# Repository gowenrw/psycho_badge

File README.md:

# psycho_badge

This is where all the files for psycho_badge will be stored.

This includes code and art and cad and fab files.  All the things.

## File Structure

This is the file structure of this repository

* [/](/README.md) <- YOU ARE HERE
* [/3d_parts/](./3d_parts/) - 3D models of parts used in this project
* [/art/](./art/) - Artwork and other graphics created by this project
  * [/art/fonts/](./art/fonts/) - Fonts used in art and graphics
  * [/art/inspiration/](./art/inspiration/) - Art and graphics pulled from other sources used as inspiration for this project
  * [/art/logos/](./art/logos/) - Logos used in this project
* [/code/](./code/) - All project related Code / Firmware
* [/docs/](./docs/) - Documentation created by this project including web pages
* [/eda/](./eda/) - Electronic Design Automation files (i.e. KiCad)
  * [/eda/psycho_badge/](./eda/psycho_badge/) - KiCad 9.x project folder for the psycho_badge PCB
* [/reference_parts/](./reference_parts/) - Submodule of Third Party Documentation related to components
* [./README.md](/README.md) - This File
* [./LICENSE](/LICENSE) - Currently set to MIT

Note: the reference_parts directory is a link to a submodule repository.
To add it use the following cmd after cloning this:
```
git submodule add https://github.com/gowenrw/reference_parts reference_parts
```
This will make a link to the current commit of that repo.
To update it to a newer commit after its been added use this cmd:
```
git submodule update --init --recursive
```

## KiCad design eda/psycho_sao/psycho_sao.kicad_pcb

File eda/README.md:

# Electronic Design Automation

This is where all the Electronic Design Automation files for the PCB(s) will be stored.
The EDA used is KiCad 9.x unless otherwise specified.

The KiCad projects have been configured to use local libraries for long term sustainability per the best practices listed [HERE](https://hackaday.com/2017/05/18/kicad-best-practises-library-management/) and elsewhere.

## File Structure

This is the file structure of this repository

* [/](/README.md) - Home
* [/eda](/eda/) - Electronic Design Automation files - YOU ARE HERE
  * [/eda/psycho_badge/](/eda/psycho_badge/) - KiCad 9.x project folder for the psycho_badge PCB
    * ./3d_models/ - This directory contains footprint 3d model files
    * ./gerber/ - This directory contains gerber formatted files for manufacturing
    * ./lib_fp/ - This directory contains footprint module directories
    * ./lib_sh/ - This directory contains schematic library files
    * ./snapshots/ - This directory contains prints of schematic / cad files and images of preview / final product
  * [/eda/psycho_sao/](/eda/psycho_sao/) - KiCad 9.x project folder for the psycho_badge SAO PCBs
    * ./3d_models/ - This directory contains footprint 3d model files
    * ./gerber/ - This directory contains gerber formatted files for manufacturing
    * ./lib_fp/ - This directory contains footprint module directories
    * ./lib_sh/ - This directory contains schematic library files
    * ./snapshots/ - This directory contains prints of schematic / cad files and images of preview / final product

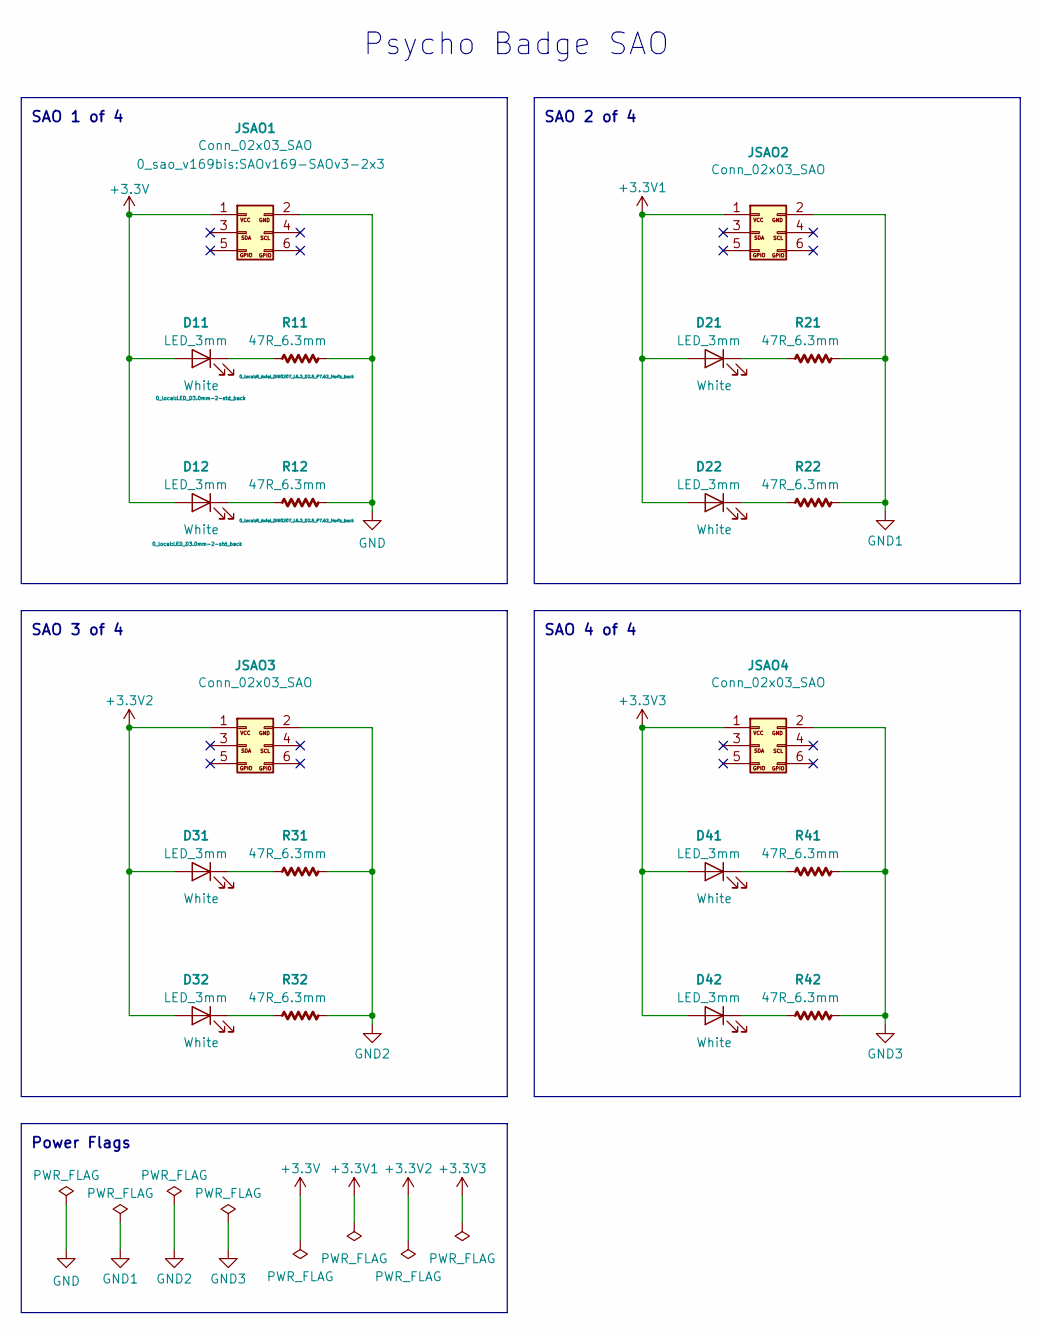
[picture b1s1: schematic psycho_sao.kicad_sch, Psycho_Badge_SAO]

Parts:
D11, D12, D21, D22, D31, D32, D41, D42: LED_3mm; LED_D3.0mm-2-std_back
JSAO1, JSAO2, JSAO3, JSAO4: Conn_02x03_SAO; SAOv169-SAOv3-2x3
R11, R12, R21, R22, R31, R32, R41, R42: 47R_6.3mm; R_Axial_DIN0207_L6.3_D2.5_P7.62_Horiz_back

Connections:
+3.3V: D11.2 (A), D12.2 (A), JSAO1.1
+3.3V1: D21.2 (A), D22.2 (A), JSAO2.1
+3.3V2: D31.2 (A), D32.2 (A), JSAO3.1
+3.3V3: D41.2 (A), D42.2 (A), JSAO4.1
GND: JSAO1.2, R11.2, R12.2
GND1: JSAO2.2, R21.2, R22.2
GND2: JSAO3.2, R31.2, R32.2
GND3: JSAO4.2, R41.2, R42.2
unnamed: D11.1 (K), R11.1
unnamed: D12.1 (K), R12.1
unnamed: D21.1 (K), R21.1
unnamed: D22.1 (K), R22.1
unnamed: D31.1 (K), R31.1
unnamed: D32.1 (K), R32.1
unnamed: D41.1 (K), R41.1
unnamed: D42.1 (K), R42.1

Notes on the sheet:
SAO 1 of 4
SAO 4 of 4
Psycho Badge SAO
Power Flags
SAO 3 of 4
SAO 2 of 4

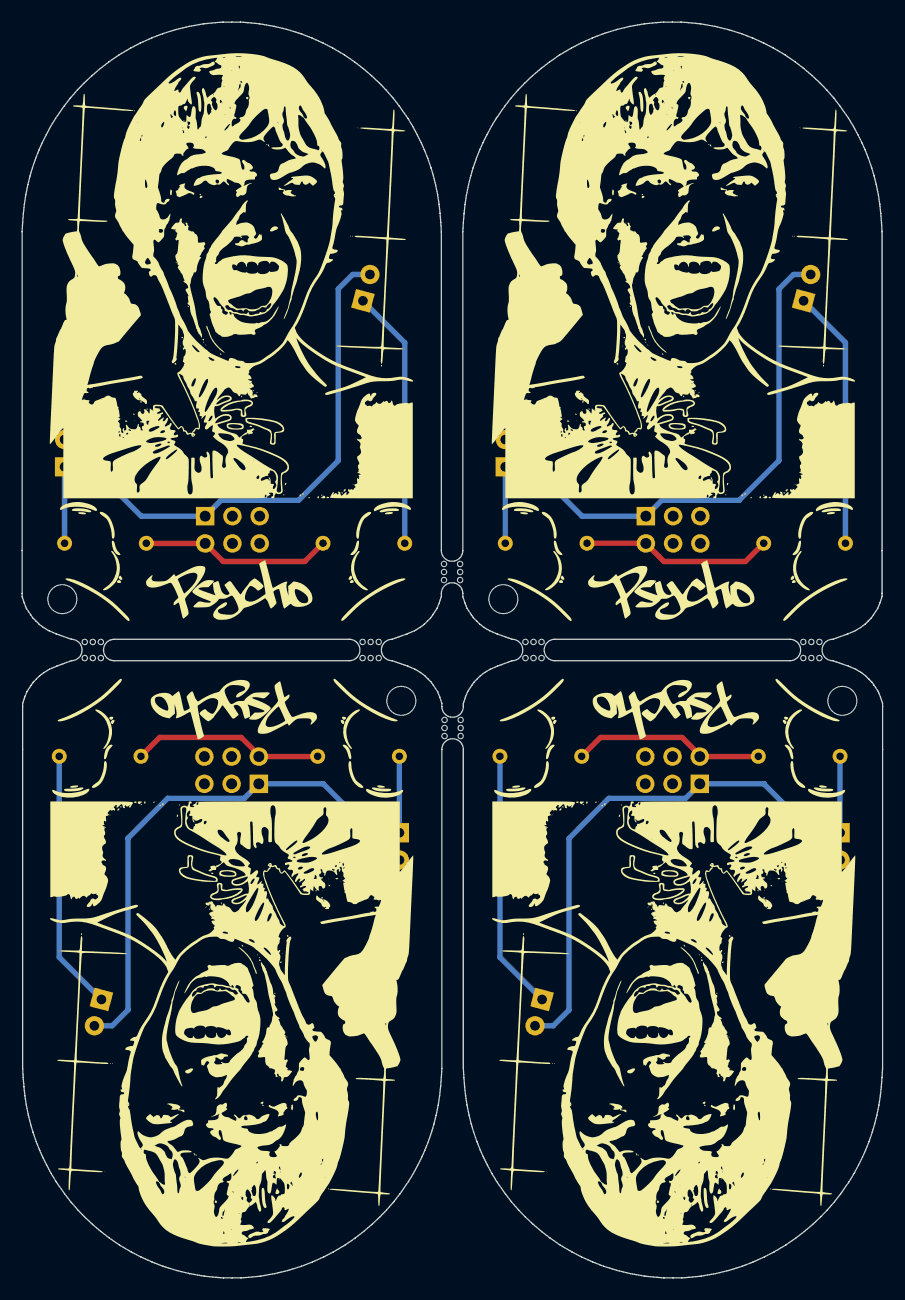
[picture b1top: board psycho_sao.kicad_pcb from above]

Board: 2 copper layers, 80.2 x 117.1 mm, 33 parts (0 on the bottom side), 16 nets.

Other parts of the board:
Fold: LED_Fold_Indicator_1; LED_Fold_Indicator_back
Fold#2, Fold#3, Fold#4, Fold#5, Fold#6, Fold#7, Fold#8: LED_Fold_Indicator_1; LED_Fold_Indicator_back
Psycho_BMask: Psycho_BMask; Scream_Face_B_Mask
Psycho_FCu: Psycho_FCu; Scream_Face_F_Cu
Psycho_FMask: Psycho_FMask; Scream_Face_F_Mask
Psycho_FSilk: Psycho_FSilk; Scream_Face_F_Silk
sao_edgecuts_02: Edge Cuts; SAO_edgecuts_02

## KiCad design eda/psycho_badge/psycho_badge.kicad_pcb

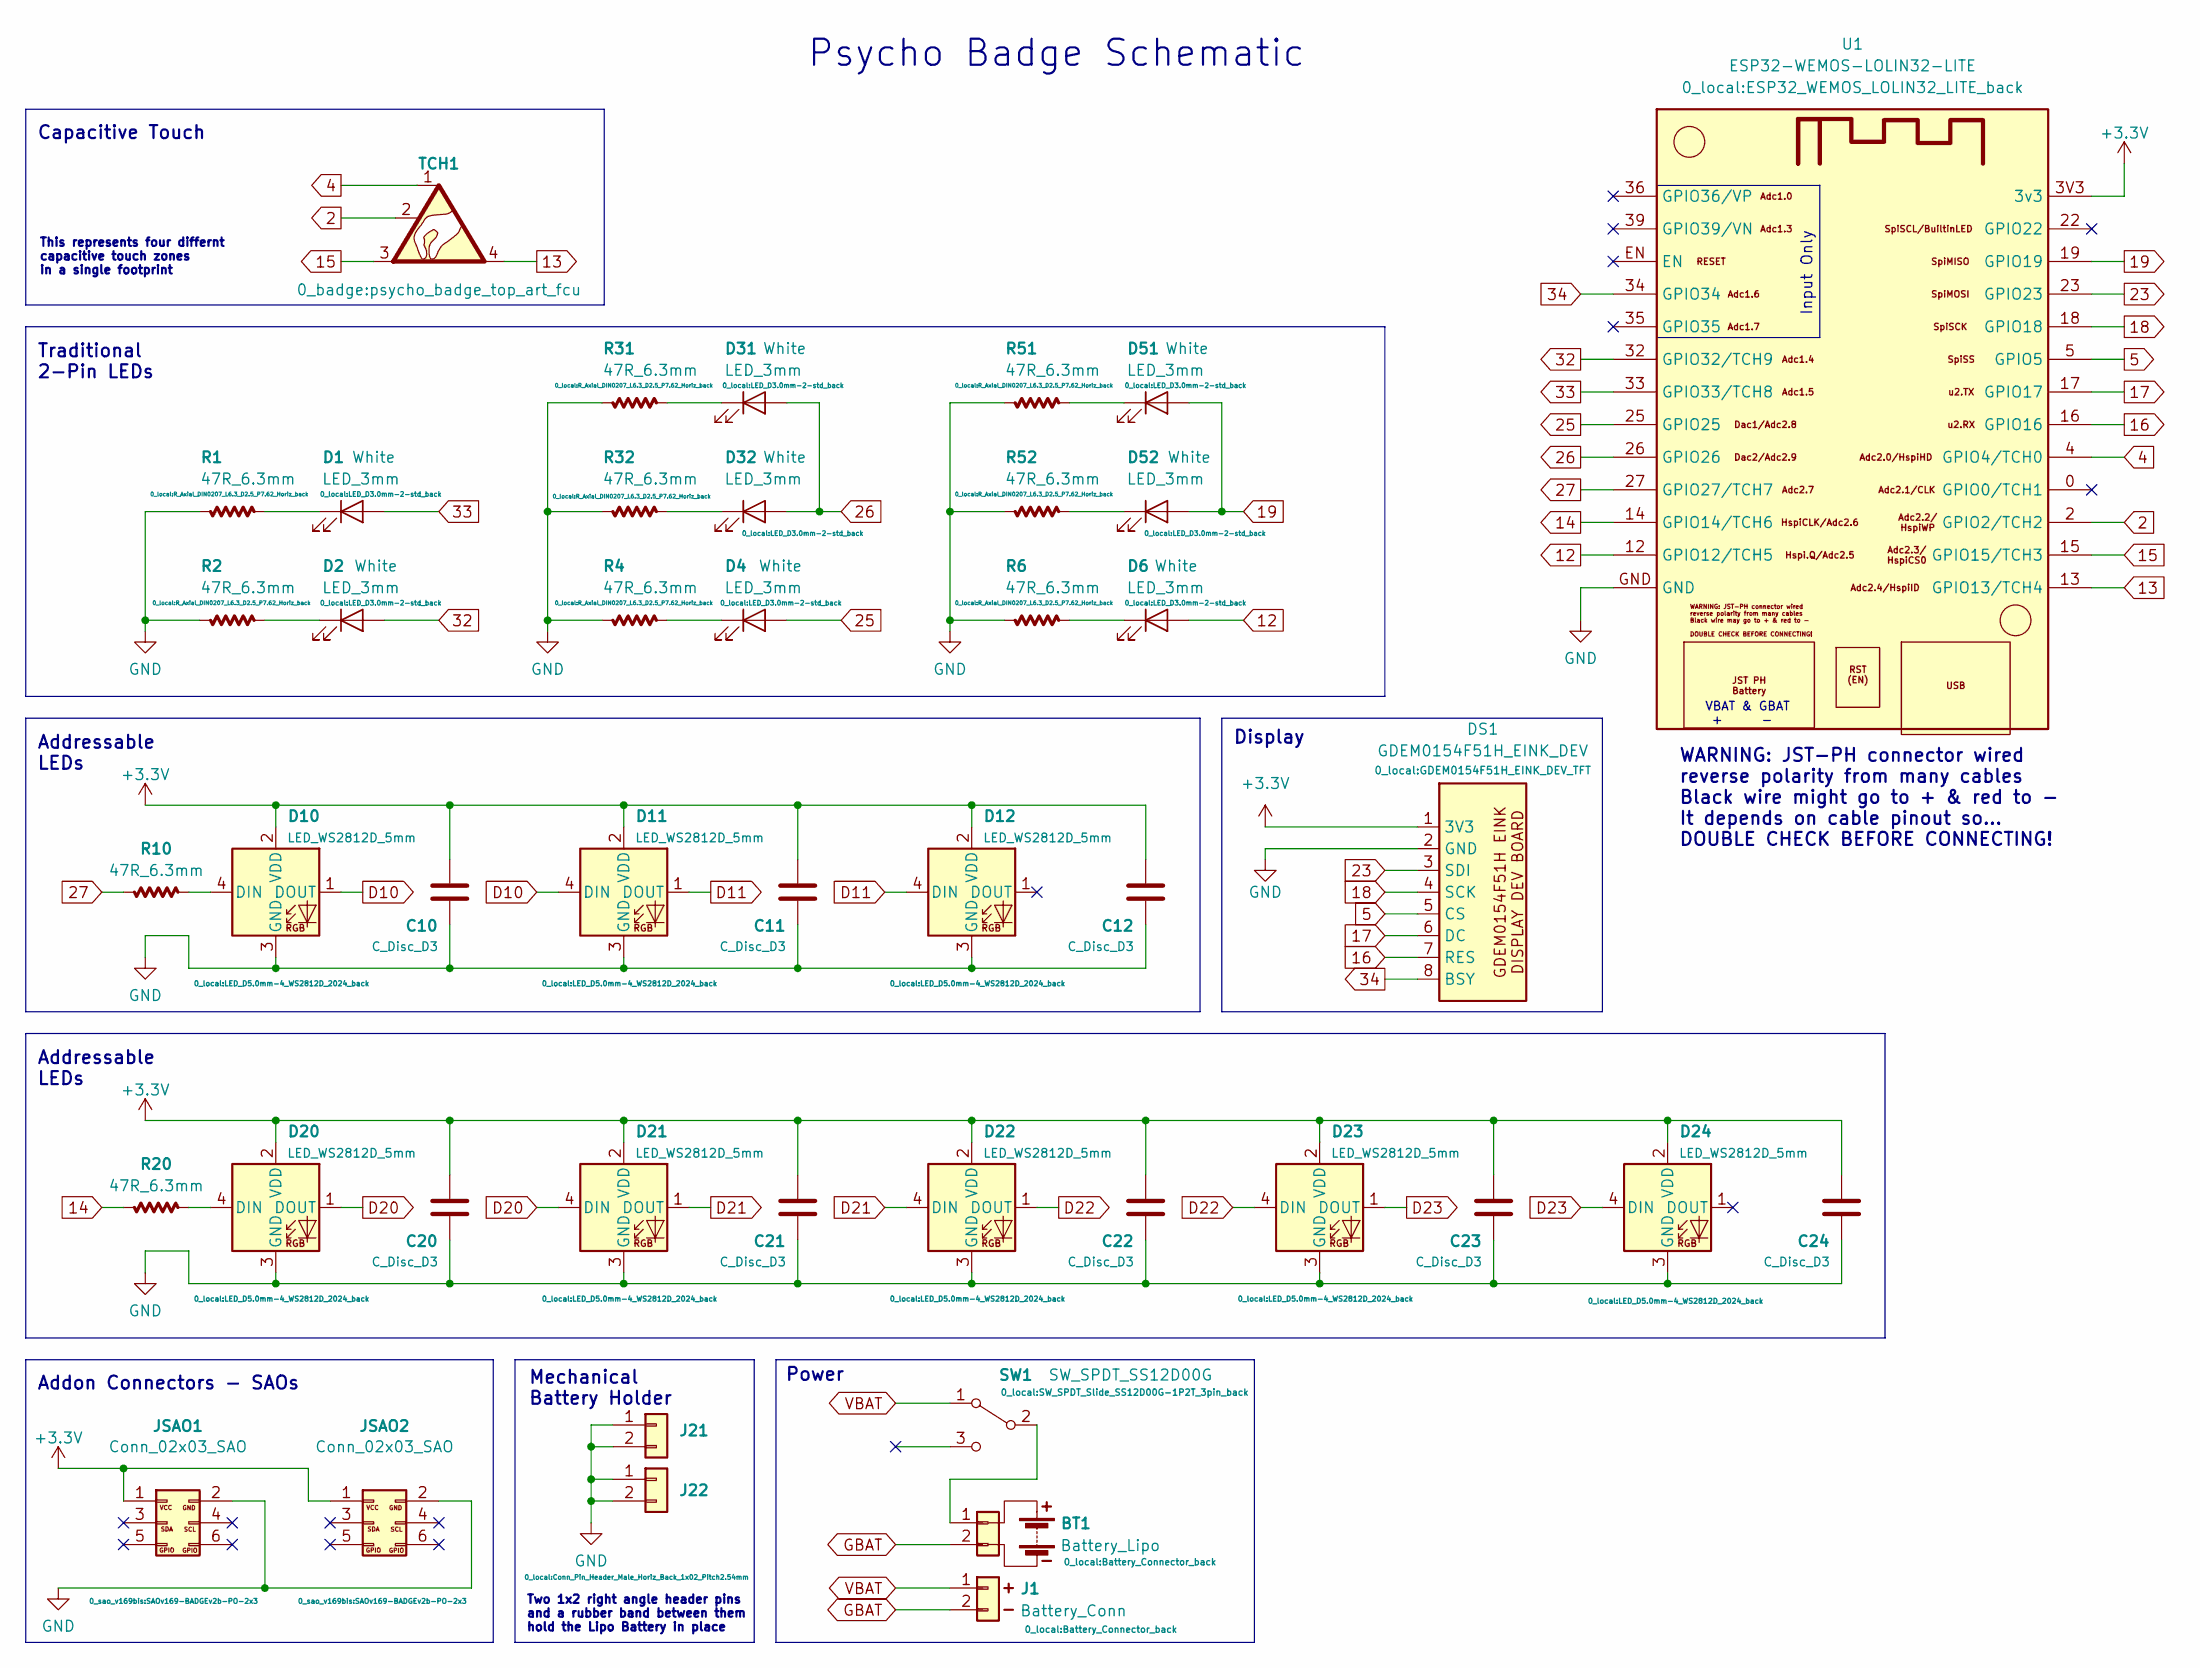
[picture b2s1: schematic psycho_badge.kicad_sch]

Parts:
BT1: Battery_Lipo; Battery_Connector_back
C10, C11, C12, C20, C21, C22, C23, C24: C_Disc_D3; C_Disc_D3_back
D1, D2, D4, D6, D31, D32, D51, D52: LED_3mm; LED_D3.0mm-2-std_back
D10, D11, D12, D20, D21, D22, D23, D24: LED_WS2812D_5mm; LED_D5.0mm-4_WS2812D_2024_back
DS1: GDEM0154F51H_EINK_DEV; GDEM0154F51H_EINK_DEV_TFT
J1: Battery_Conn; Battery_Connector_back
J21, J22: 01x02; Conn_Pin_Header_Male_Horiz_Back_1x02_Pitch2.54mm
JSAO1, JSAO2: Conn_02x03_SAO; SAOv169-BADGEv2b-PO-2x3
R1, R2, R4, R6, R10, R20, R31, R32, R51, R52: 47R_6.3mm; R_Axial_DIN0207_L6.3_D2.5_P7.62_Horiz_back
SW1: SW_SPDT_SS12D00G; SW_SPDT_Slide_SS12D00G-1P2T_3pin_back
TCH1: SYM_Touch_lg_x4; psycho_badge_top_art_fcu
U1: ESP32-WEMOS-LOLIN32-LITE; ESP32_WEMOS_LOLIN32_LITE_back

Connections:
2: TCH1.2, U1.2 (GPIO2/TCH2)
4: TCH1.1, U1.4 (GPIO4/TCH0)
5: DS1.5 (CS), U1.5 (GPIO5)
12: D6.2 (A), U1.12 (GPIO12/TCH5)
13: TCH1.4, U1.13 (GPIO13/TCH4)
14: R20.2, U1.14 (GPIO14/TCH6)
15: TCH1.3, U1.15 (GPIO15/TCH3)
16: DS1.7 (RES), U1.16 (GPIO16)
17: DS1.6 (DC), U1.17 (GPIO17)
18: DS1.4 (SCK), U1.18 (GPIO18)
19: D51.2 (A), D52.2 (A), U1.19 (GPIO19)
23: DS1.3 (SDI), U1.23 (GPIO23)
25: D4.2 (A), U1.25 (GPIO25)
26: D31.2 (A), D32.2 (A), U1.26 (GPIO26)
27: R10.2, U1.27 (GPIO27/TCH7)
32: D2.2 (A), U1.32 (GPIO32/TCH9)
33: D1.2 (A), U1.33 (GPIO33/TCH8)
34: DS1.8 (BSY), U1.34 (GPIO34)
+3.3V: C10.1, C11.1, C12.1, C20.1, C21.1, C22.1, C23.1, C24.1, D10.2 (VDD), D11.2 (VDD), D12.2 (VDD), D20.2 (VDD), D21.2 (VDD), D22.2 (VDD), D23.2 (VDD), D24.2 (VDD), DS1.1 (3V3), JSAO1.1, JSAO2.1, U1.3V3 (3v3)
D10: D10.1 (DOUT), D11.4 (DIN)
D11: D11.1 (DOUT), D12.4 (DIN)
D20: D20.1 (DOUT), D21.4 (DIN)
D21: D21.1 (DOUT), D22.4 (DIN)
D22: D22.1 (DOUT), D23.4 (DIN)
D23: D23.1 (DOUT), D24.4 (DIN)
GBAT: BT1.2, J1.2
GND: C10.2, C11.2, C12.2, C20.2, C21.2, C22.2, C23.2, C24.2, D10.3 (GND), D11.3 (GND), D12.3 (GND), D20.3 (GND), D21.3 (GND), D22.3 (GND), D23.3 (GND), D24.3 (GND), DS1.2 (GND), J21.1, J21.2, J22.1, J22.2, JSAO1.2, JSAO2.2, R1.2, R2.2, R4.2, R6.2, R31.2, R32.2, R51.2, R52.2, U1.GND
unnamed: BT1.1, SW1.2 (B)
unnamed: D1.1 (K), R1.1
unnamed: D2.1 (K), R2.1
unnamed: D4.1 (K), R4.1
unnamed: D6.1 (K), R6.1
unnamed: D10.4 (DIN), R10.1
unnamed: D20.4 (DIN), R20.1
unnamed: D31.1 (K), R31.1
unnamed: D32.1 (K), R32.1
unnamed: D51.1 (K), R51.1
unnamed: D52.1 (K), R52.1
VBAT: J1.1, SW1.1 (A)

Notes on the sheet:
Power
Traditional 2-Pin LEDs
This represents four differnt capacitive touch zones in a single footprint
Input Only
Two 1x2 right angle header pins and a rubber band between them hold the Lipo Battery in place
VBAT & GBAT + -
Mechanical Battery Holder
Addressable LEDs
Addon Connectors - SAOs
WARNING: JST-PH connector wired reverse polarity from many cables Black wire might go to + & red to - It depends on cable pinout so... DOUBLE CHECK BEFORE CONNECTING!
Psycho Badge Schematic
Capacitive Touch
Display

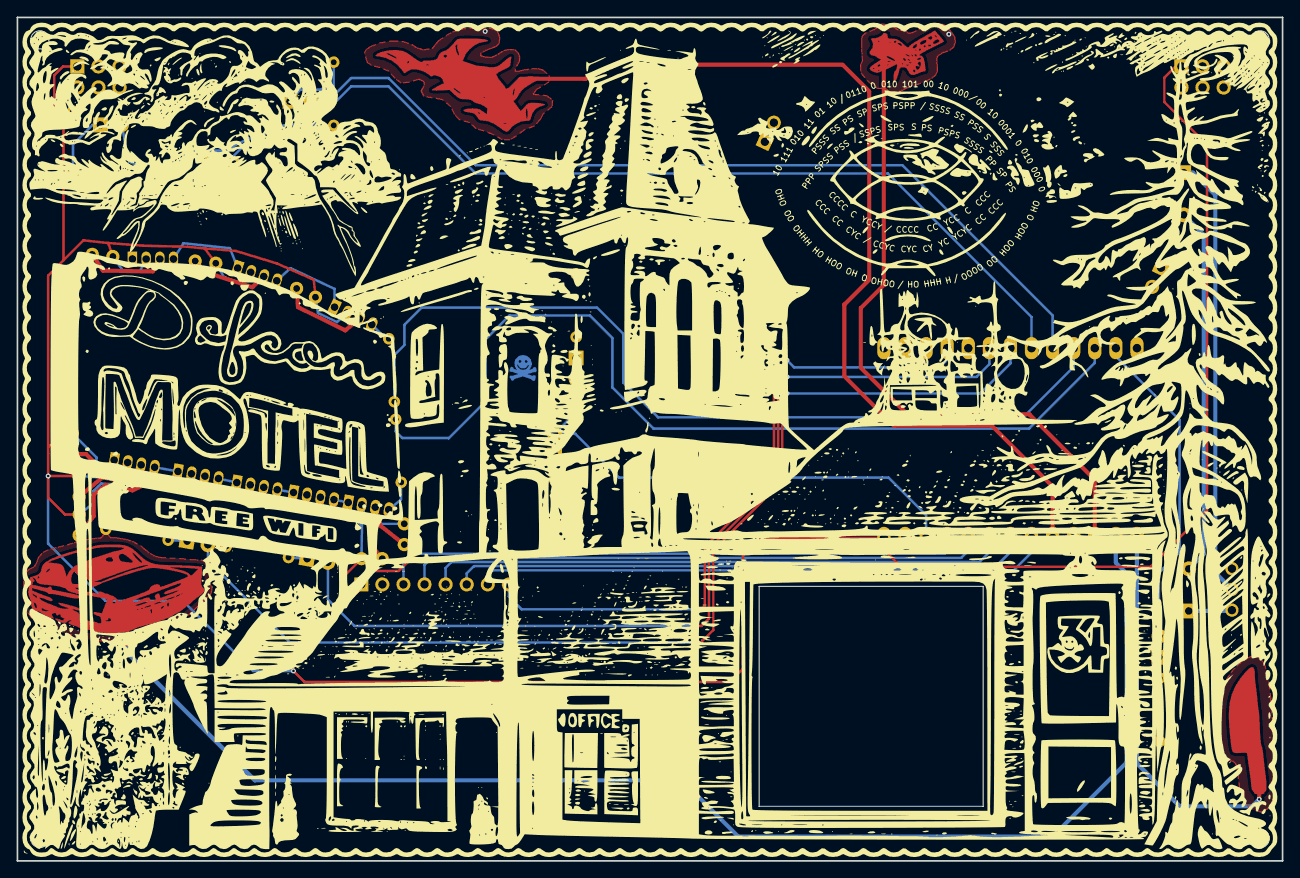
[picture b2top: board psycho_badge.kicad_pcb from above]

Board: 2 copper layers, 152.4 x 101.6 mm, 55 parts (0 on the bottom side), 39 nets.

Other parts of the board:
Fold: LED_Fold_Indicator_1; LED_Fold_Indicator_back
Fold#2, Fold#3, Fold#4, Fold#5, Fold#6, Fold#7, Fold#8, Fold#9: LED_Fold_Indicator_1; LED_Fold_Indicator_back
G-FMask: LOGO; psycho_badge_top_art_fmsk
G-Silk: LOGO; psycho_badge_top_art

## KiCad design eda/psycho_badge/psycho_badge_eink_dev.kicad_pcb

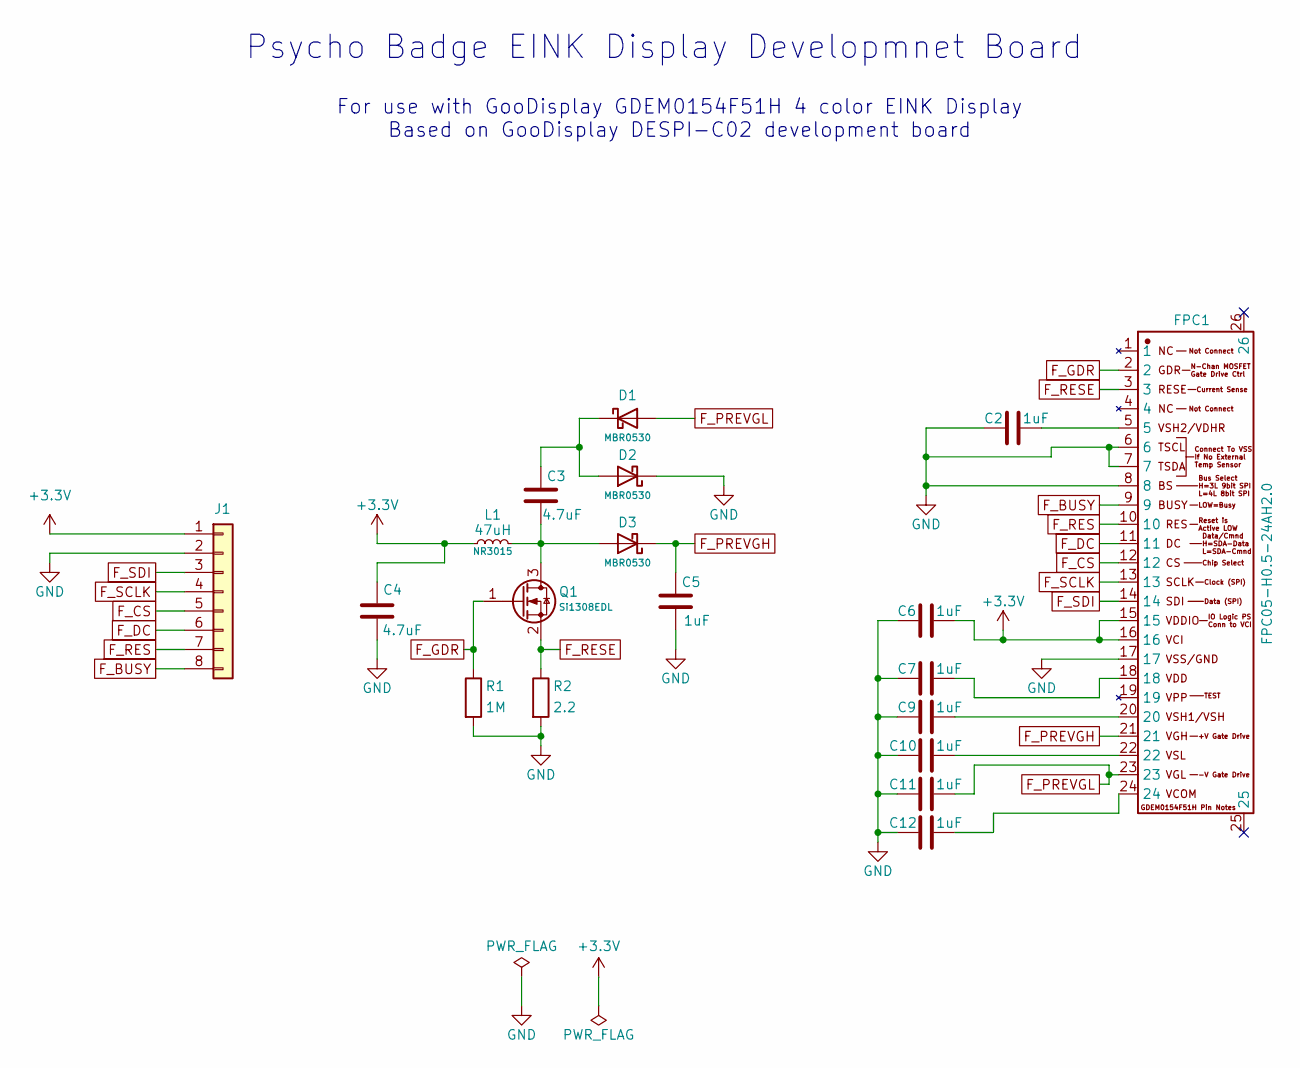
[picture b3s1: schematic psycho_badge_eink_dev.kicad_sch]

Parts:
C2, C5, C6, C7, C9, C10, C11, C12: 1uF; C_0805_2012Metric
C3, C4: 4.7uF; C_0805_2012Metric
D1, D2, D3: MBR0530; D_SOD-123
FPC1: FPC05-H0.5-24AH2.0; FPC-SMD_24P-P0.50_FPC05-H0.5-24AH2.0; Manufacturer Part FPC05-H0.5-24AH2.0
J1: Conn_01x08; Conn_Pin_Header_Straight_1x08_Pitch2.54mm
L1: 47uH; L_APV_ANR3015
Q1: Si1308EDL; SOT-323_SC-70
R1: 1M; R_0805_2012Metric
R2: 2.2; R_0805_2012Metric

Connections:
+3.3V: C4.2, C6.2, FPC1.15, FPC1.16, J1.1, L1.1
F_BUSY: FPC1.9, J1.8
F_CS: FPC1.12, J1.5
F_DC: FPC1.11, J1.6
F_GDR: FPC1.2, Q1.1 (G), R1.1
F_PREVGH: C5.2, D3.1 (K), FPC1.21
F_PREVGL: C11.2, D1.2 (A), FPC1.23
F_RES: FPC1.10, J1.7
F_RESE: FPC1.3, Q1.2 (S), R2.1
F_SCLK: FPC1.13, J1.4
F_SDI: FPC1.14, J1.3
GND: C2.1, C4.1, C5.1, C6.1, C7.1, C9.1, C10.1, C11.1, C12.1, D2.1 (K), FPC1.6, FPC1.7, FPC1.8, FPC1.17, J1.2, R1.2, R2.2
unnamed: C2.2, FPC1.5
unnamed: C7.2, FPC1.18
unnamed: C9.2, FPC1.20
unnamed: C10.2, FPC1.22
unnamed: C12.2, FPC1.24
unnamed: C3.2, D1.1 (K), D2.2 (A)
unnamed: C3.1, D3.2 (A), L1.2, Q1.3 (D)

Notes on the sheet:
For use with GooDisplay GDEM0154F51H 4 color EINK Display Based on GooDisplay DESPI-C02 development board
Psycho Badge EINK Display Developmnet Board

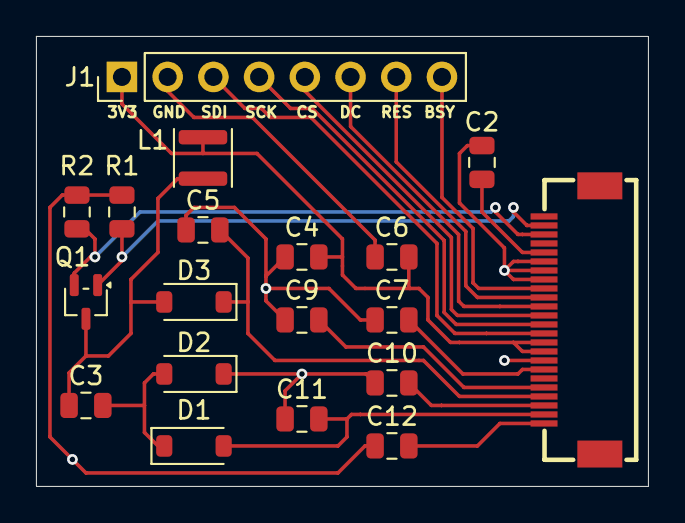
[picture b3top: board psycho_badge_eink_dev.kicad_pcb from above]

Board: 2 copper layers, 34.0 x 25.0 mm, 19 parts (0 on the bottom side), 19 nets.

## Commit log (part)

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2025-05-31 initial content push
2025-06-01 psycho badge art and eda updates
2025-08-24 pre dc33 updates
2026-03-13 lumilor docs
2026-04-09 component updates
2026-04-14 component update
2026-04-21 added eink display circuit and dev board
2026-04-24 eink dev board final
2026-05-26 added code base for testing
2026-05-27 eink code
2026-05-28 art updates
2026-06-22 component layout done
2026-06-24 .gitignore scratch directories
    Currently, just any directory called "testing".
2026-06-24 pcb tracing
2026-06-29 main pcb complete
2026-06-29 Add files via upload
    These are the 4 copies of the blank SAO boards with all the artwork removed
2026-06-29 Psycho SAO (take 2)
    Psycho SAO folder upload. Target dir is eda/psycho_sao
2026-06-29 Psycho SAO Upload
    The template files for SAO boards. Hopefully all 8 files are included in this PR...
2026-06-30 main badge pcb updates
2026-06-30 pcb updates
2026-06-30 pcb updates... final?
